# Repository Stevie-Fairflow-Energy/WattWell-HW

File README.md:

# Aim of the project
WattWell - An inverter, built for a lifetime. 
A home inverter, to interface battery systems and PV systems with the UK and EU electricity grids.

The WattWell must be:
- Durable
- Repairable
- Open-Source

The main goal of the project is to develop an open source inverter (Hardware and Software).  
The initial configuration of the project will be a single phase, 5 kW inverter. 

An important part of the project is to be able to work with different types of switching components (IGBT/MOSFET). Nowadays, we often see that inverters are replaced after 10 years but they keep working or some faulty inverters that are not easily repared because the design is not modular or easy to fix.

Then, the goal is to design an Open Source inverter that is modular to be easy to be fixed and flexible enough to have differents functionalities (batteries/PV/...)

The project will be divided into different "workpackages" based on the functional blocks needed to make the whole system work. These functional blocks are called "Modules", and may be split into further modules where necessary. The diagram below shows the module definitions we are currently working to. 

1. Supervisory control: development of the main control board able to get the measurements, generate references, ... This board embeds the main mcu.
2. Inverter Board
3. DC/DC converter: Able to take a variable DC input (48V +/- 20%) and output a stable DC output controllable between 360 V and 500 V.
4. DC Link: A DC link capable of self-protection
5. A DC filter for smooth input/output
6. DC Protections for over-current and over-voltage protection
7. DC connections for physically connecting the DC source to WattWell
8.  AC filter for smooth sine wave input/output
9. AC protection for over-current and over-voltage protection. Required for compatibility with grid codes.
10. Connections for phsyically conecting the external electrical system to WattWell
11. Human Machine Interface (HMI) to act as the interface between the user and the supervisory control

For the Inverter board, two sub-modules are assumed:
1. Control and Driver board: interface between the supervisory control board and power switch (IGBT's/Mosfet's). The driver board needs to generate the PWM signals based on a reference from the supervisor.
2. Power circuit: power circuit of the inverter

# Expected functionalities

- Being able (and allowed) to be connected to the European grid
- MPPT for solar panels (with DC/DC)
- Battery connection
- Communication capabilities (serial,...)
- Working in islanding mode (offgrid)

# 1. Supervisory control board:

For the supervisory control, the firmware on the main mcu should have (main mcu based on STM32G434):

1. Low level drivers
2. Basics functionalities (bootloader, debug uart, pll,...)
3. Advanced functionalities (power management, MPPT, state machine)

The main control board will be able to measure:
1.  3AC voltages (max 400V) - ADC min 14bits
2.  2DC voltages (max 1500V) -ADC min 14bits
3.  4AC/DC current measurement - ADC min 14bits
4.  Temperature measurement

The main control board will have the following interface:
1.  2X UART(1X to RS485; 1X to USB)
2.  1xSPI
3.  2xI2C
4.  1xCAN
5.  6X PWM's
6.  6X DO's
7.  6X DI's
8.  6X AI'S (temp from IGBT/Mos)

Other functions:
1.  Debug LED
2.  RTC (supercap based)
3.  Additionnal ROM (TBD)
4.  Watchdog
5.  Power supply for IGBT's/Mosfets

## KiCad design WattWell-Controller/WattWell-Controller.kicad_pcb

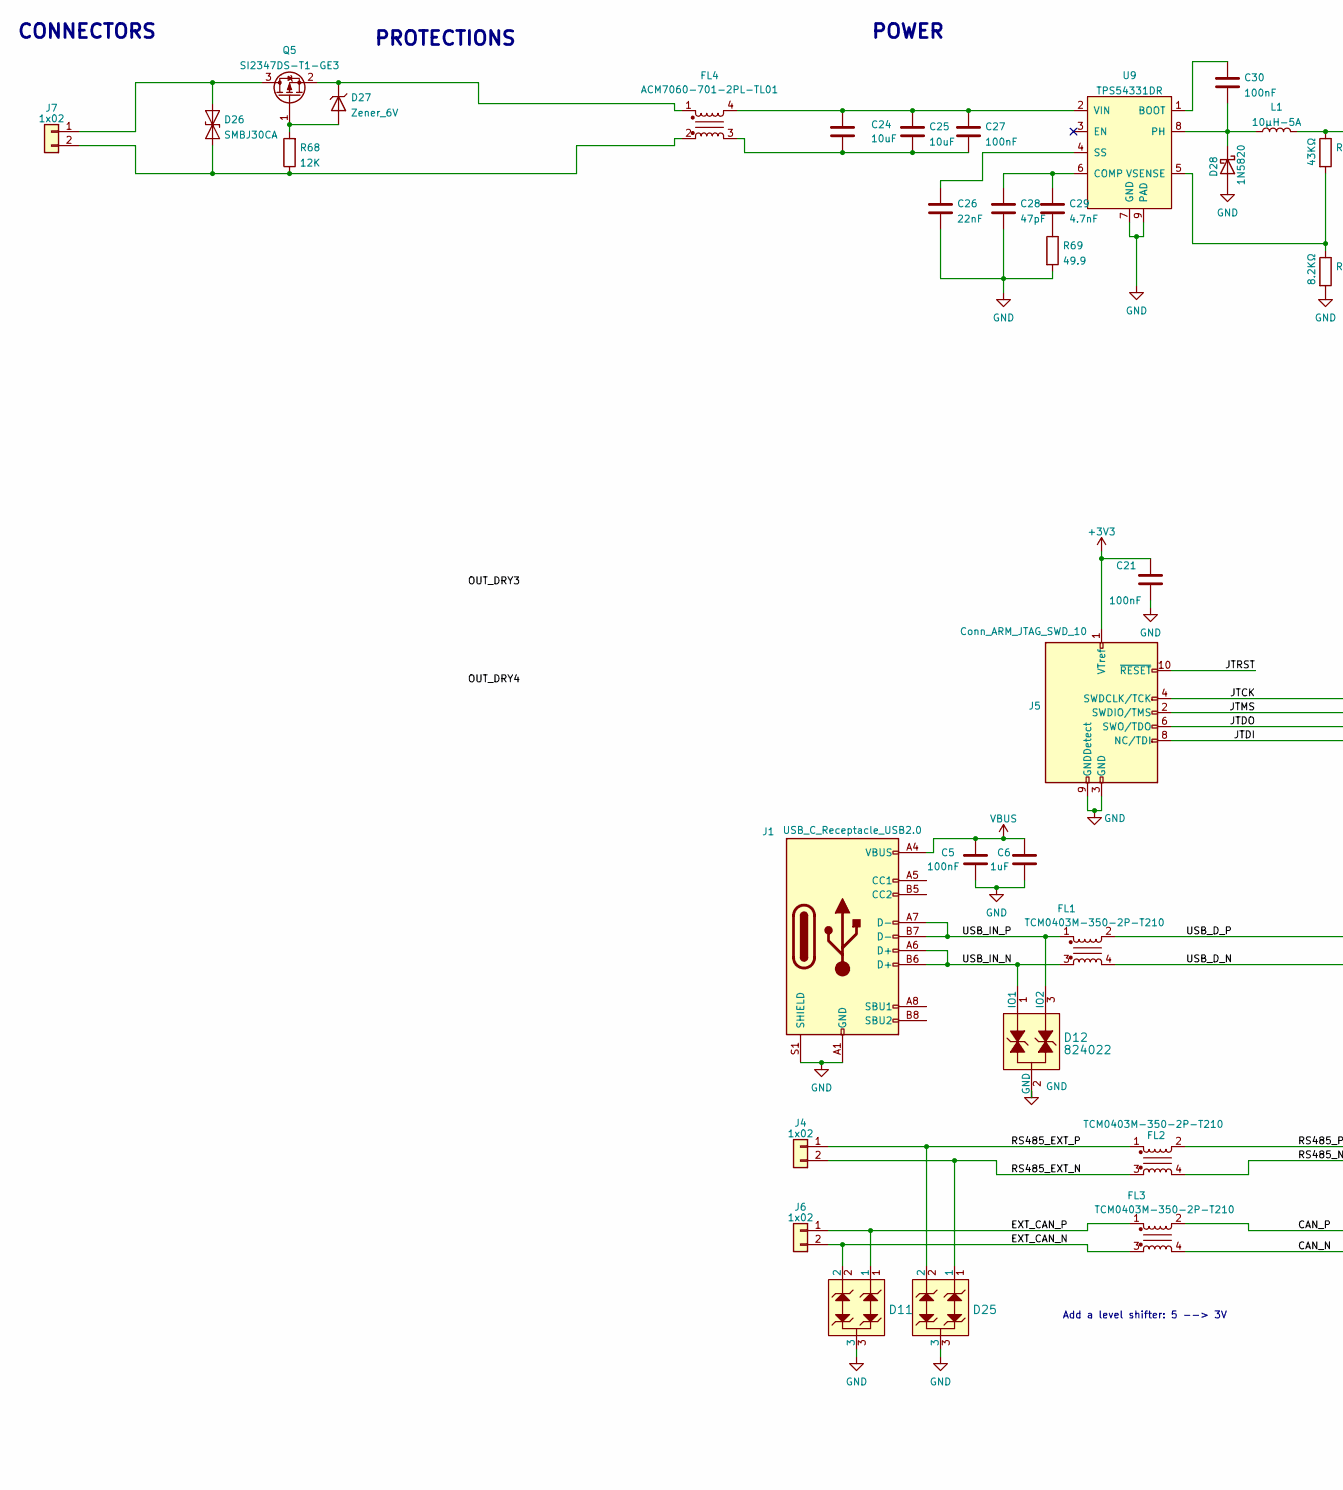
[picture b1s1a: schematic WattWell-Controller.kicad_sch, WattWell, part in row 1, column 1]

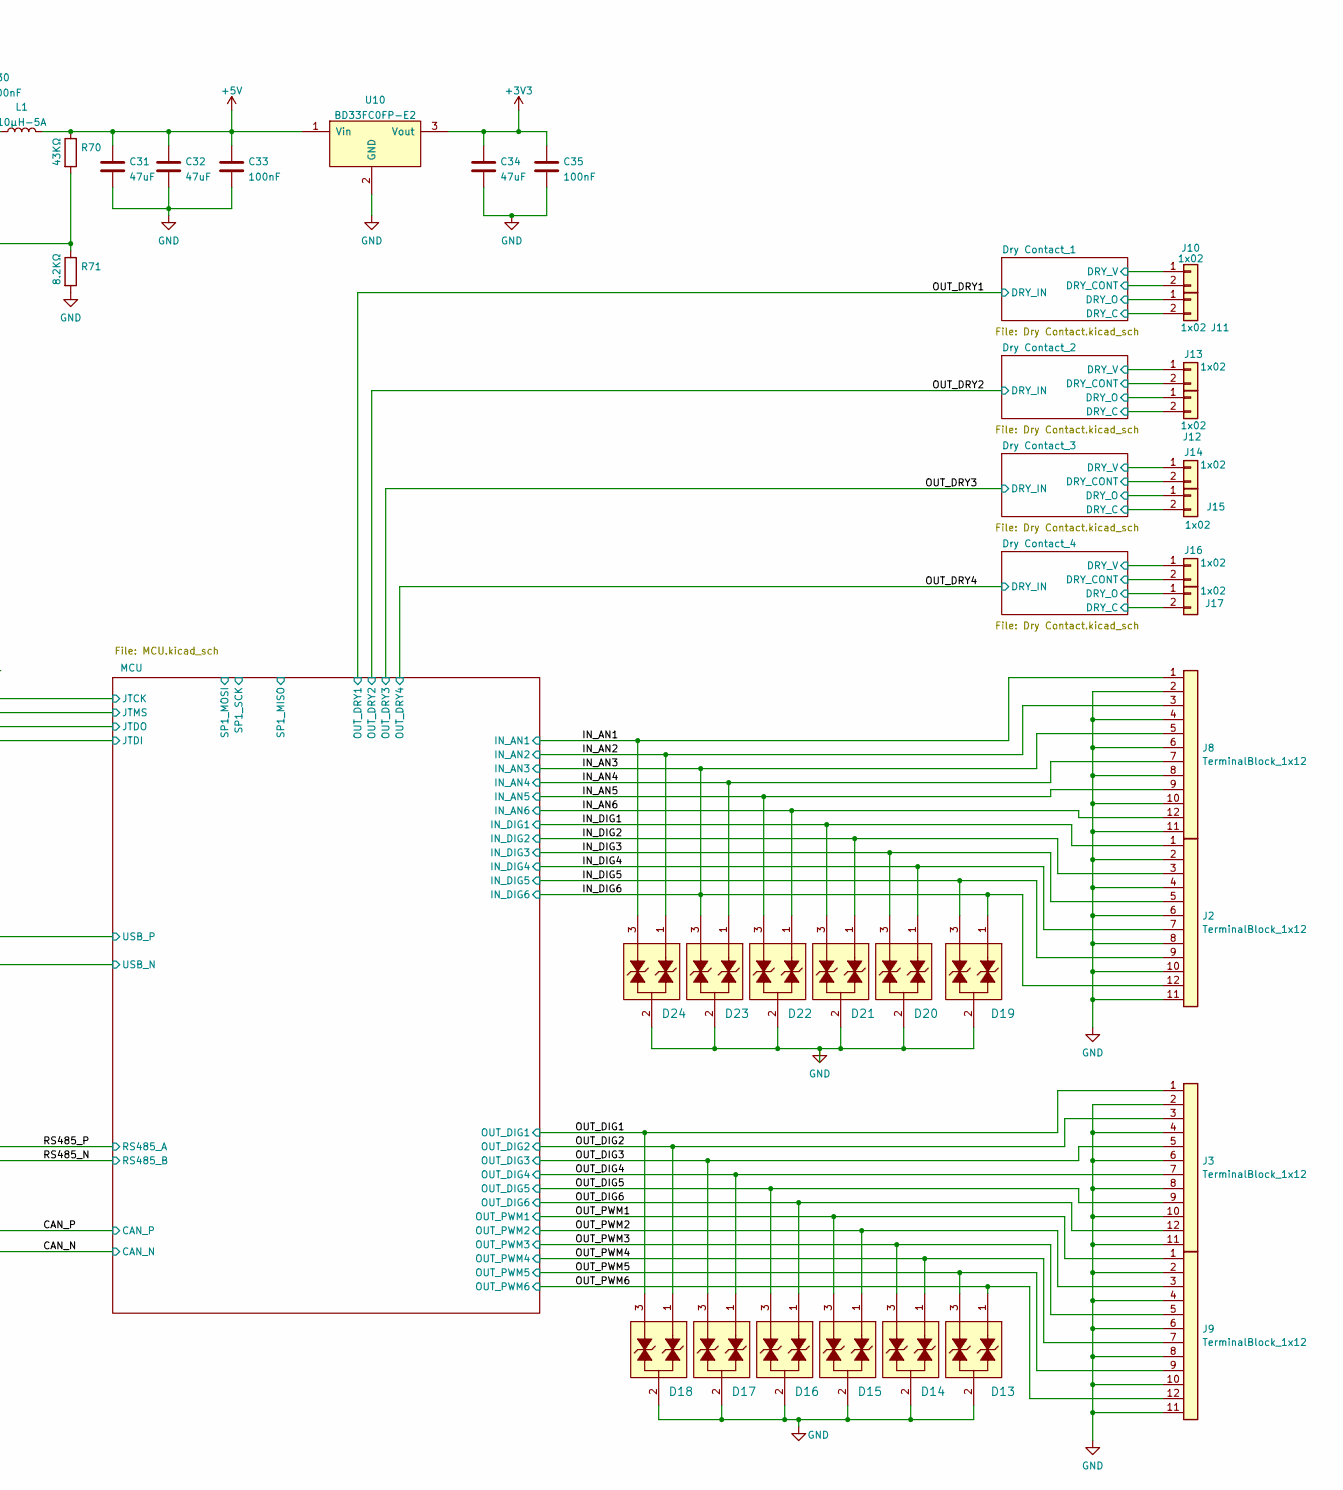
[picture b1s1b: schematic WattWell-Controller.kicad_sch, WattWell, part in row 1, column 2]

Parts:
C5, C21, C27, C30, C33, C35: 100nF; C_0603_1608Metric; Tolerance 10%; Voltage 50V; MPN CL10B104KB8NNNC
C6: 1uF; C_0603_1608Metric; Tolerance 10%; Voltage 25V; MPN CL10B105KA8NNNC
C24, C25: 10uF; C_1206_3216Metric; Tolerance 20%; Voltage 50V; MPN GRT31CR61H106ME01L
C26: 22nF; C_0603_1608Metric; Tolerance 10%; Voltage 50V; MPN CL10B223KB8WPNC
C28: 47pF; C_0603_1608Metric; Tolerance 10%; Voltage 50V; MPN 885012006055
C29: 4.7nF; C_0603_1608Metric; Tolerance 10%; Voltage 50V; MPN CL10B472KB8NNNC
C31, C32, C34: 47uF; C_1206_3216Metric; Tolerance 10%; Voltage 10V; MPN GRT31CR61A476KE13L
D11, D25: TVS_2-Channel-7V; SOT-23; MPN CDSOT23-SM712
D12: 824022; SOT-23; MPN 824022
D13, D14, D15, D16, D17, D18, D19, D20, D21, D22, D23, D24: PESD3V3L2BT; SOT-23; MPN PESD3V3L2BT,215
D26: SMBJ30CA; D_SMB; MPN SMBJ30CA
D27: Zener_6V; D_SOD-123; Voltage 6V; MPN MMSZ5233B-E3-08
D28: 1N5820; D_DO-201AD_P15.24mm_Horizontal
FL1, FL2, FL3: TCM0403M-350-2P-T210; Choke_TDK_TCM0403M-350-2P-T210; Manufacturer Part Number TCM0403M-350-2P-T210
FL4: ACM7060-701-2PL-TL01; ChokeSMD_ACM7060; MPN ACM7060-701-2PL-TL01
J1: USB_C_Receptacle_USB2.0; USB_C_Receptacle_GCT_USB4105-xx-A_16P_TopMnt_Horizontal; MPN USB4105-GF-A-120
J2, J3, J8, J9: TerminalBlock_1x12; TerminalBlock_Phoenix_MKDS-3-12-5.08_1x12_P5.08mm_Horizontal; MPN 1795763
J4, J6, J7, J10, J11, J12, J13, J14, J15, J16, J17: 1x02; WURTH-691312510002; MPN 691312510002
J5: Conn_ARM_JTAG_SWD_10; PinHeader_2x05_P2.54mm_Vertical_SMD; MPN FTSH-105-01-L-DV-K
L1: 10μH-5A; Inductor_Wurth_XHMI-6060; MPN 74439346100
Q5: SI2347DS-T1-GE3; SOT-23; MPN SI2347DS-T1-GE3
R68: 12K; R_0603_1608Metric; MPN RT0603FRE0712KL
R69: 49.9; R_0603_1608Metric; Tolerance 1%; MPN TNPW020149R9BEED
R70: 43KΩ; R_0603_1608Metric; Tolerance 1%; MPN RC0603FR-0743KL
R71: 8.2KΩ; R_0603_1608Metric; Tolerance 1%; MPN ERJ-3EKF8201V
U9: TPS54331DR; SOIC-8-1EP_3.9x4.9mm_P1.27mm_EP2.29x3mm_ThermalVias; MPN TPS54331DR
U10: BD33FC0FP-E2; TO-252-2; MPN BD33FC0FP-E2

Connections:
+3V3: C21.1, C34.1, C35.1, J5.1 (VTref), U10.3 (Vout); also elsewhere on the board
+5V: C31.1, C32.1, C33.1, L1.2, R70.1, U10.1 (Vin); also elsewhere on the board
/CAN_N: FL3.4; also elsewhere on the board
/CAN_P: FL3.2; also elsewhere on the board
/Dry Contact_1/DRY1_C: J11.2; also elsewhere on the board
/Dry Contact_1/DRY1_O: J11.1; also elsewhere on the board
/Dry Contact_1/DRY_CONT: J10.2; also elsewhere on the board
/Dry Contact_1/DRY_V: J10.1; also elsewhere on the board
/Dry Contact_2/DRY1_C: J12.2; also elsewhere on the board
/Dry Contact_2/DRY1_O: J12.1; also elsewhere on the board
/Dry Contact_2/DRY_CONT: J13.2; also elsewhere on the board
/Dry Contact_2/DRY_V: J13.1; also elsewhere on the board
/Dry Contact_3/DRY1_C: J15.2; also elsewhere on the board
/Dry Contact_3/DRY1_O: J15.1; also elsewhere on the board
/Dry Contact_3/DRY_CONT: J14.2; also elsewhere on the board
/Dry Contact_3/DRY_V: J14.1; also elsewhere on the board
/Dry Contact_4/DRY1_C: J17.2; also elsewhere on the board
/Dry Contact_4/DRY1_O: J17.1; also elsewhere on the board
/Dry Contact_4/DRY_CONT: J16.2; also elsewhere on the board
/Dry Contact_4/DRY_V: J16.1; also elsewhere on the board
/EXT_CAN_N: D11.2, FL3.3, J6.2
/EXT_CAN_P: D11.1, FL3.1, J6.1
/IN_AN1: D24.3, J8.1; also elsewhere on the board
/IN_AN2: D24.1, J8.3; also elsewhere on the board
/IN_AN3: D19.1, D23.3, J2.12 (Pin_8), J8.5; also elsewhere on the board
/IN_AN4: D23.1, J8.7 (Pin_10); also elsewhere on the board
/IN_AN5: D22.3, J8.9 (Pin_12); also elsewhere on the board
/IN_AN6: D22.1, J8.12 (Pin_8); also elsewhere on the board
/IN_DIG1: D21.3, J2.1; also elsewhere on the board
/IN_DIG2: D21.1, J2.3; also elsewhere on the board
/IN_DIG3: D20.3, J2.5; also elsewhere on the board
/IN_DIG4: D20.1, J2.7 (Pin_10); also elsewhere on the board
/IN_DIG5: D19.3, J2.9 (Pin_12); also elsewhere on the board
/JTCK: J5.4 (SWDCLK/TCK); also elsewhere on the board
/JTDI: J5.8 (NC/TDI); also elsewhere on the board
/JTDO: J5.6 (SWO/TDO); also elsewhere on the board
/JTMS: J5.2 (SWDIO/TMS); also elsewhere on the board
/JTRST: J5.10 (~RESET)
/OUT_DIG1: D18.3, J3.1; also elsewhere on the board
/OUT_DIG2: D18.1, J3.3; also elsewhere on the board
/OUT_DIG3: D17.3, J3.5; also elsewhere on the board
/OUT_DIG4: D17.1, J3.7 (Pin_10); also elsewhere on the board
/OUT_DIG5: D16.3, J3.9 (Pin_12); also elsewhere on the board
/OUT_DIG6: D16.1, J3.12 (Pin_8); also elsewhere on the board
/OUT_PWM1: D15.3, J9.1; also elsewhere on the board
/OUT_PWM2: D15.1, J9.3; also elsewhere on the board
/OUT_PWM3: D14.3, J9.5; also elsewhere on the board
/OUT_PWM4: D14.1, J9.7 (Pin_10); also elsewhere on the board
/OUT_PWM5: D13.3, J9.9 (Pin_12); also elsewhere on the board
/OUT_PWM6: D13.1, J9.12 (Pin_8); also elsewhere on the board
/RS485_EXT_N: D25.1, FL2.3, J4.2
/RS485_EXT_P: D25.2, FL2.1, J4.1
/RS485_N: FL2.4; also elsewhere on the board
/RS485_P: FL2.2; also elsewhere on the board
/USB_D_N: FL1.4; also elsewhere on the board
/USB_D_P: FL1.2; also elsewhere on the board
/USB_IN_N: D12.1 (IO1), FL1.3, J1.A6 (D+), J1.B6 (D+)
/USB_IN_P: D12.3 (IO2), FL1.1, J1.A7 (D-), J1.B7 (D-)
GND: C5.2, C6.2, C21.2, C26.2, C28.2, C31.2, C32.2, C33.2, C34.2, C35.2, D11.3, D12.2 (GND), D13.2, D14.2, D15.2, D16.2, D17.2, D18.2, D19.2, D20.2, D21.2, D22.2, D23.2, D24.2, D25.3, D28.2 (A), J1.A1 (GND), J1.A12 (GND), J1.B1 (GND), J1.B12 (GND), J1.S1 (SHIELD), J2.2, J2.4, J2.6, J2.8 (Pin_11), J2.10 (Pin_13), J2.11 (Pin_7), J3.2, J3.4, J3.6, J3.8 (Pin_11), J3.10 (Pin_13), J3.11 (Pin_7), J5.3 (GND), J5.5 (GND), J5.9 (GNDDetect), J8.2, J8.4, J8.6, J8.8 (Pin_11), J8.10 (Pin_13), J8.11 (Pin_7), J9.2, J9.4, J9.6, J9.8 (Pin_11), J9.10 (Pin_13), J9.11 (Pin_7), R69.2, R71.2, U9.7 (GND), U9.9 (PAD), U10.2 (GND); also elsewhere on the board
unnamed: C24.2, C25.2, C27.2, FL4.3
unnamed: C29.2, R69.1
unnamed: D26.1 (A1), FL4.2, J7.2, R68.1
unnamed: D26.2 (A2), J7.1, Q5.3 (D)
unnamed: D27.2 (A), Q5.1 (G), R68.2
unnamed: D27.1 (K), FL4.1, Q5.2 (S)
unnamed: C30.2, D28.1 (K), L1.1, U9.8 (PH)
unnamed: C30.1, U9.1 (BOOT)
unnamed: C28.1, C29.1, U9.6 (COMP)
unnamed: C26.1, U9.4 (SS)
unnamed: C24.1, C25.1, C27.1, FL4.4, U9.2 (VIN)
unnamed: R70.2, R71.1, U9.5 (VSENSE)
VBUS: C5.1, C6.1, J1.A4 (VBUS), J1.A9 (VBUS), J1.B4 (VBUS), J1.B9 (VBUS); also elsewhere on the board

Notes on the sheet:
CONNECTORS
POWER
Add a level shifter: 5 --> 3V
PROTECTIONS

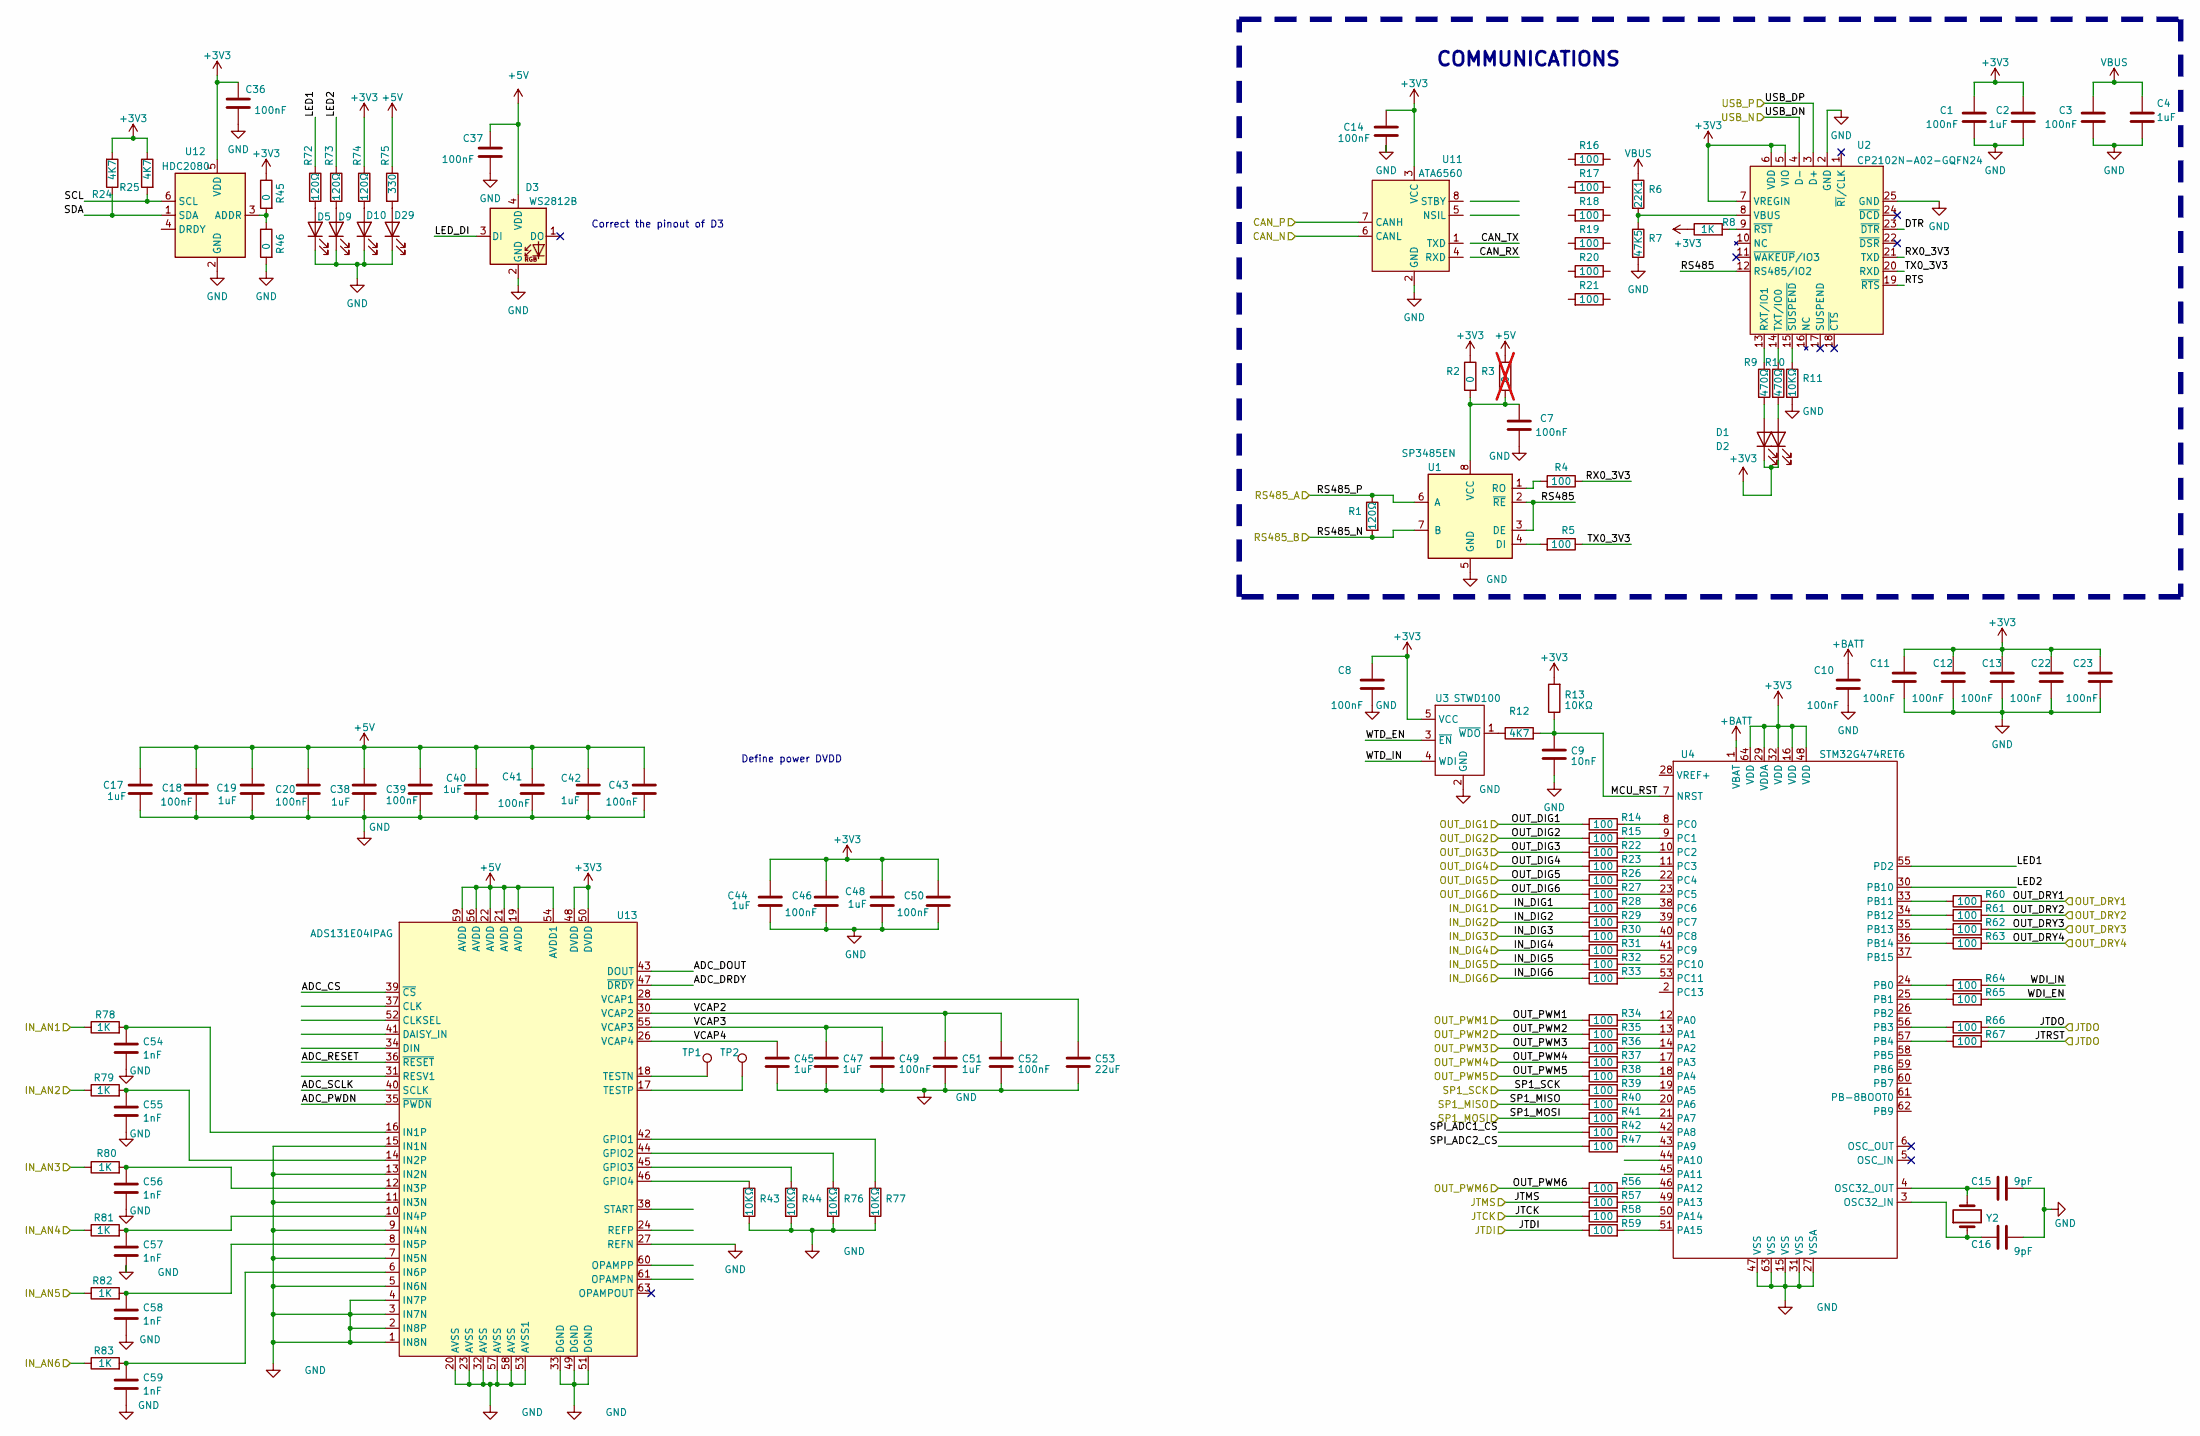
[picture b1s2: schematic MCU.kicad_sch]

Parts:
C1, C3, C7, C8, C10, C11, C12, C13, C14, C18, C20, C22, C23, C36, C37, C39, C41, C43, C46, C49, C50, C52: 100nF; C_0603_1608Metric; Tolerance 10%; Voltage 50V; MPN CL10B104KB8NNNC
C2, C4, C17, C19, C38, C40, C42, C44, C45, C47, C48, C51: 1uF; C_0603_1608Metric; Tolerance 10%; Voltage 25V; MPN CL10B105KA8NNNC
C9: 10nF; C_0603_1608Metric; Tolerance 10%; Voltage 50V; MPN CL10B103KB8NNNC
C15, C16: 9pF; C_0603_1608Metric; Tolerance 0.5%; Voltage 50VDC; MPN 0603N9R0D500CT
C53: 22uF; C_1206_3216Metric; Tolerance 20%; Voltage 10V; MPN CL31B226MPHNNNE
C54, C55, C56, C57, C58, C59: 1nF; C_0603_1608Metric; Tolerance 10%; Voltage 50V; MPN CL10B102KB8NNNC
D1, D2: LED_Small; LED_0603_1608Metric; MPN 150060RS55040
D3: WS2812B; LED_WS2812B_PLCC4_5.0x5.0mm_P3.2mm; Manufacturer Part Number 4684
D5, D9, D10, D29: 150060RS55040; LED_0603_1608Metric; MPN 150060RS55040
R1, R72, R73, R74: 120Ω; R_0603_1608Metric; Tolerance 5%; MPN CR0603-FX-1200ELF
R2, R45, R46: 0; R_0603_1608Metric; MPN RC0603JR-070RL
R3: 0; R_0603_1608Metric; MPN RC0603JR-070RL; not fitted
R4, R5, R14, R15, R16, R17, R18, R19, R20, R21, R22, R23, R26, R27, R28, R29, R30, R31, R32, R33, R34, R35, R36, R37, R38, R39, R40, R41, R42, R47, R56, R57, R58, R59, R60, R61, R62, R63, R64, R65, R66, R67: 100; R_0603_1608Metric; Tolerance 1%; MPN RC0603FR-07100RL
R6: 22K1; R_0603_1608Metric; MPN CR0603-FX-2212ELF
R7: 47K5; R_0603_1608Metric; MPN RT0603DRE0747K5L
R8, R78, R79, R80, R81, R82, R83: 1K; R_0603_1608Metric; Tolerance 1%; MPN RC0603FR-071KL
R9, R10: 470Ω; R_0603_1608Metric; Tolerance 5%; MPN CRCW0603470RJNEBC
R11, R13, R43, R44, R76, R77: 10KΩ; R_0603_1608Metric; Tolerance 1%; MPN ERJ-3EKF1002V
R12, R24, R25: 4K7; R_0603_1608Metric; Tolerance 1%; MPN CRGH0603F4K7
R75: 330; R_0603_1608Metric; Tolerance 1%; MPN AF0402JR-07330RL
TP1, TP2: TestPoint_1.5mm; TestPoint_Pad_D1.5mm
U1: SP3485EN; SOIC-8_3.9x4.9mm_P1.27mm; Manufacturer Part Number MAX3072EASA+
U2: CP2102N-A02-GQFN24; QFN-24-1EP_4x4mm_P0.5mm_EP2.6x2.6mm; MPN CP2102N-A02-GQFN24
U3: STWD100; SOT-23-5; Manufacturer Part Number STWD100YNWWY3F
U4: LQFP-64_10x10mm_P0.5mm; Manufacturer Part Number STM32G474RET6
U11: ATA6560; SOIC-8_3.9x4.9mm_P1.27mm; Manufacturer Part Number ATA6560-GAQW-N
U12: HDC2080; Texas_PWSON-N6; MPN HDC2080DMBT
U13: LQFP-64_10x10mm_P0.5mm; MPN ADS131E04IPAG
Y2: Crystal; Oscillator_SMD_ECS_2520MV-xxx-xx-4Pin_2.5x2.0mm; MPN ECS-.327-9-34QCS-TR9

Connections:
+3V3: C1.1, C2.1, C8.1, C11.1, C12.1, C13.1, C14.1, C22.1, C23.1, C36.1, C44.1, C46.1, C48.1, C50.1, D1.2 (K), D2.2 (K), R2.1, R8.1, R13.2, R24.2, R25.1, R45.1, R74.1, U2.5 (VIO), U2.6 (VDD), U2.7 (VREGIN), U3.5 (VCC), U4.16 (VDD), U4.29 (VDDA), U4.32 (VDD), U4.48 (VDD), U4.64 (VDD), U11.3 (VCC), U12.5 (VDD), U13.48 (DVDD), U13.50 (DVDD); also elsewhere on the board
+5V: C17.1, C18.1, C19.1, C20.1, C37.1, C38.1, C39.1, C40.1, C41.1, C42.1, C43.1, D3.4 (VDD), R3.1, R75.1, U13.19 (AVDD), U13.21 (AVDD), U13.22 (AVDD), U13.54 (AVDD1), U13.56 (AVDD), U13.59 (AVDD); also elsewhere on the board
+BATT: C10.1, U4.1 (VBAT)
/CAN_N: U11.6 (CANL); also elsewhere on the board
/CAN_P: U11.7 (CANH); also elsewhere on the board
/IN_AN1: R78.1; also elsewhere on the board
/IN_AN2: R79.1; also elsewhere on the board
/IN_AN3: R33.1, R80.1; also elsewhere on the board
/IN_AN4: R81.1; also elsewhere on the board
/IN_AN5: R82.1; also elsewhere on the board
/IN_AN6: R83.1; also elsewhere on the board
/IN_DIG1: R28.1; also elsewhere on the board
/IN_DIG2: R29.1; also elsewhere on the board
/IN_DIG3: R30.1; also elsewhere on the board
/IN_DIG4: R31.1; also elsewhere on the board
/IN_DIG5: R32.1; also elsewhere on the board
/JTCK: R58.1; also elsewhere on the board
/JTDI: R59.1; also elsewhere on the board
/JTDO: R66.2, R67.2; also elsewhere on the board
/JTMS: R57.1; also elsewhere on the board
/MCU/ADC_CS: U13.39 (~CS)
/MCU/ADC_DOUT: U13.43 (DOUT)
/MCU/ADC_DRDY: U13.47 (~DRDY)
/MCU/ADC_PWDN: U13.35 (~PWDN)
/MCU/ADC_RESET: U13.36 (~RESET)
/MCU/ADC_SCLK: U13.40 (SCLK)
/MCU/DTR: U2.23 (~DTR)
/MCU/LED1: R72.1, U4.55 (PD2)
/MCU/LED2: R73.1, U4.30 (PB10)
/MCU/LED_DI: D3.3 (DI)
/MCU/MCU_RST: C9.2, R12.2, R13.1, U4.7 (NRST)
/MCU/RS485: U1.2 (~RE), U1.3 (DE), U2.12 (RS485/IO2)
/MCU/RTS: U2.19 (~RTS)
/MCU/RX0_3V3: R4.1, U2.21 (TXD)
/MCU/SCL: R25.2, U12.6 (SCL)
/MCU/SDA: R24.1, U12.1 (SDA)
/MCU/SP1_MISO: R40.1
/MCU/SP1_MOSI: R41.1
/MCU/SP1_SCK: R39.1
/MCU/SPI_ADC1_CS: R42.1
/MCU/SPI_ADC2_CS: R47.1
/MCU/TX0_3V3: R5.1, U2.20 (RXD)
/MCU/VCAP2: C51.1, C52.1, U13.30 (VCAP2)
/MCU/VCAP3: C47.1, C49.1, U13.55 (VCAP3)
/MCU/VCAP4: C45.1, U13.26 (VCAP4)
/MCU/WDI_EN: R65.2
/MCU/WDI_IN: R64.2
/MCU/WTD_EN: U3.3 (~EN)
/MCU/WTD_IN: U3.4 (WDI)
/OUT_DIG1: R14.1; also elsewhere on the board
/OUT_DIG2: R15.1; also elsewhere on the board
/OUT_DIG3: R22.1; also elsewhere on the board
/OUT_DIG4: R23.1; also elsewhere on the board
/OUT_DIG5: R26.1; also elsewhere on the board
/OUT_DIG6: R27.1; also elsewhere on the board
/OUT_DRY1: R60.2; also elsewhere on the board
/OUT_DRY2: R61.2; also elsewhere on the board
/OUT_DRY3: R62.2; also elsewhere on the board
/OUT_DRY4: R63.2; also elsewhere on the board
/OUT_PWM1: R34.1; also elsewhere on the board
/OUT_PWM2: R35.1; also elsewhere on the board
/OUT_PWM3: R36.1; also elsewhere on the board
/OUT_PWM4: R37.1; also elsewhere on the board
/OUT_PWM5: R38.1; also elsewhere on the board
/OUT_PWM6: R56.1; also elsewhere on the board
/RS485_N: R1.2, U1.7 (B); also elsewhere on the board
/RS485_P: R1.1, U1.6 (A); also elsewhere on the board
/USB_D_N: U2.4 (D-); also elsewhere on the board
/USB_D_P: U2.3 (D+); also elsewhere on the board
GND: C1.2, C2.2, C3.2, C4.2, C7.2, C8.2, C9.1, C10.2, C11.2, C12.2, C13.2, C14.2, C15.2, C16.2, C17.2, C18.2, C19.2, C20.2, C22.2, C23.2, C36.2, C37.2, C38.2, C39.2, C40.2, C41.2, C42.2, C43.2, C44.2, C45.2, C46.2, C47.2, C48.2, C49.2, C50.2, C51.2, C52.2, C53.2, C54.2, C55.2, C56.2, C57.2, C58.2, C59.2, D3.2 (GND), D5.2 (K), D9.2 (K), D10.2 (K), D29.2 (K), R7.2, R11.2, R43.2, R44.2, R46.2, R76.2, R77.2, U1.5 (GND), U2.2 (GND), U2.25 (GND), U3.2 (GND), U4.15 (VSS), U4.27 (VSSA), U4.31 (VSS), U4.47 (VSS), U4.63 (VSS), U11.2 (GND), U12.2 (GND), U13.1 (IN8N), U13.2 (IN8P), U13.3 (IN7N), U13.4 (IN7P), U13.5 (IN6N), U13.7 (IN5N), U13.9 (IN4N), U13.11 (IN3N), U13.13 (IN2N), U13.15 (IN1N), U13.20 (AVSS), U13.23 (AVSS), U13.27 (REFN), U13.32 (AVSS), U13.33 (DGND), U13.49 (DGND), U13.51 (DGND), U13.53 (AVSS1), U13.57 (AVSS), U13.58 (AVSS); also elsewhere on the board
unnamed: D1.1 (A), R9.2
unnamed: D2.1 (A), R10.2
unnamed: D5.1 (A), R72.2
unnamed: D9.1 (A), R73.2
unnamed: D10.1 (A), R74.2
unnamed: D29.1 (A), R75.2
unnamed: R5.2, U1.4 (DI)
unnamed: R4.2, U1.1 (RO)
unnamed: C7.1, R2.2, R3.2, U1.8 (VCC)
unnamed: R9.1, U2.13 (RXT/IO1)
unnamed: R10.1, U2.14 (TXT/IO0)
unnamed: R6.2, R7.1, U2.8 (VBUS)
unnamed: R8.2, U2.9 (~RST)
unnamed: R11.1, U2.15 (~SUSPEND)
unnamed: R12.1, U3.1 (~WDO)
unnamed: C16.1, U4.3 (OSC32_IN), Y2.1
unnamed: C15.1, U4.4 (OSC32_OUT), Y2.2
unnamed: R34.2, U4.12 (PA0)
unnamed: R35.2, U4.13 (PA1)
unnamed: R36.2, U4.14 (PA2)
unnamed: R37.2, U4.17 (PA3)
unnamed: R38.2, U4.18 (PA4)
unnamed: R39.2, U4.19 (PA5)
unnamed: R40.2, U4.20 (PA6)
unnamed: R41.2, U4.21 (PA7)
unnamed: R42.2, U4.42 (PA8)
unnamed: R47.2, U4.43 (PA9)
unnamed: R56.2, U4.46 (PA12)
unnamed: R57.2, U4.49 (PA13)
unnamed: R58.2, U4.50 (PA14)
unnamed: R59.2, U4.51 (PA15)
unnamed: R64.1, U4.24 (PB0)
unnamed: R65.1, U4.25 (PB1)
unnamed: R66.1, U4.56 (PB3)
unnamed: R67.1, U4.57 (PB4)
unnamed: R60.1, U4.33 (PB11)
unnamed: R61.1, U4.34 (PB12)
unnamed: R62.1, U4.35 (PB13)
unnamed: R63.1, U4.36 (PB14)
unnamed: R14.2, U4.8 (PC0)
unnamed: R15.2, U4.9 (PC1)
unnamed: R22.2, U4.10 (PC2)
unnamed: R23.2, U4.11 (PC3)
unnamed: R26.2, U4.22 (PC4)
unnamed: R27.2, U4.23 (PC5)
unnamed: R28.2, U4.38 (PC6)
unnamed: R29.2, U4.39 (PC7)
unnamed: R30.2, U4.40 (PC8)
unnamed: R31.2, U4.41 (PC9)
unnamed: R32.2, U4.52 (PC10)
unnamed: R33.2, U4.53 (PC11)
unnamed: R45.2, R46.1, U12.3 (ADDR)
unnamed: R77.1, U13.42 (GPIO1)
unnamed: R76.1, U13.44 (GPIO2)
unnamed: R44.1, U13.45 (GPIO3)
unnamed: R43.1, U13.46 (GPIO4)
unnamed: C54.1, R78.2, U13.16 (IN1P)
unnamed: C55.1, R79.2, U13.14 (IN2P)
unnamed: C56.1, R80.2, U13.12 (IN3P)
unnamed: C57.1, R81.2, U13.10 (IN4P)
unnamed: C58.1, R82.2, U13.8 (IN5P)
unnamed: C59.1, R83.2, U13.6 (IN6P)
unnamed: TP1.1, U13.18 (TESTN)
unnamed: TP2.1, U13.17 (TESTP)
unnamed: C53.1, U13.28 (VCAP1)
VBUS: C3.1, C4.1, R6.1; also elsewhere on the board

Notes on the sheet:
COMMUNICATIONS
Define power DVDD
Correct the pinout of D3

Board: 2 copper layers, 225 parts (0 on the bottom side), 169 nets, no tracks yet.

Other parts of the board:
C18#2, C39#2, C46#2, C50#2: 100nF; C_0603_1608Metric
C20#2, C41#2, C43#2: 22uF; C_1206_3216Metric
D4, D6, D7, D8: 1N47xxA; D_DO-41_SOD81_P10.16mm_Horizontal
K1, K2, K3, K4: RZH3-1C4-D012; Relay_TE_RZH3-1C04-D012
Q1, Q2, Q3, Q4: MMSS8050-H-TP; SOT-23
R48, R49, R50, R51, R52, R53, R54, R55: 120Ω; R_0603_1608Metric
U5, U6, U7, U8: LTV-356T; SO-4_4.4x3.6mm_P2.54mm

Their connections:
+3V3: C46#2.1, C50#2.1; also elsewhere on the board
+5V: C18#2.1, C20#2.1, C39#2.1, C41#2.1, C43#2.1; also elsewhere on the board
/Dry Contact_1/DRY1_C: K1.12; also elsewhere on the board
/Dry Contact_1/DRY1_O: K1.14; also elsewhere on the board
/Dry Contact_1/DRY_CONT: K1.11; also elsewhere on the board
/Dry Contact_1/DRY_V: D4.1 (K), K1.A2, U5.4; also elsewhere on the board
/Dry Contact_2/DRY1_C: K2.12; also elsewhere on the board
/Dry Contact_2/DRY1_O: K2.14; also elsewhere on the board
/Dry Contact_2/DRY_CONT: K2.11; also elsewhere on the board
/Dry Contact_2/DRY_V: D6.1 (K), K2.A2, U6.4; also elsewhere on the board
/Dry Contact_3/DRY1_C: K3.12; also elsewhere on the board
/Dry Contact_3/DRY1_O: K3.14; also elsewhere on the board
/Dry Contact_3/DRY_CONT: K3.11; also elsewhere on the board
/Dry Contact_3/DRY_V: D7.1 (K), K3.A2, U7.4; also elsewhere on the board
/Dry Contact_4/DRY1_C: K4.12; also elsewhere on the board
/Dry Contact_4/DRY1_O: K4.14; also elsewhere on the board
/Dry Contact_4/DRY_CONT: K4.11; also elsewhere on the board
/Dry Contact_4/DRY_V: D8.1 (K), K4.A2, U8.4; also elsewhere on the board
/OUT_DRY1: R49.2; also elsewhere on the board
/OUT_DRY2: R51.2; also elsewhere on the board
/OUT_DRY3: R53.2; also elsewhere on the board
/OUT_DRY4: R55.2; also elsewhere on the board
GND: C18#2.2, C20#2.2, C39#2.2, C41#2.2, C43#2.2, C46#2.2, C50#2.2, U5.2, U6.2, U7.2, U8.2; also elsewhere on the board
GND1: Q1.2 (E), Q2.2 (E), Q3.2 (E), Q4.2 (E)
unnamed: D4.2 (A), K1.A1, Q1.3 (C)
unnamed: D6.2 (A), K2.A1, Q2.3 (C)
unnamed: D7.2 (A), K3.A1, Q3.3 (C)
unnamed: D8.2 (A), K4.A1, Q4.3 (C)
unnamed: Q1.1 (B), R48.1
unnamed: Q2.1 (B), R50.1
unnamed: Q3.1 (B), R52.1
unnamed: Q4.1 (B), R54.1
unnamed: R48.2, U5.3
unnamed: R49.1, U5.1
unnamed: R50.2, U6.3
unnamed: R51.1, U6.1
unnamed: R52.2, U7.3
unnamed: R53.1, U7.1
unnamed: R54.2, U8.3
unnamed: R55.1, U8.1

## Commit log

2025-01-14 Component placement continued
2025-05-28 Layout continued. Placement
2025-09-11 Placement continued Changed the order of Terminal block connectors
2025-09-12 Placement continued
2025-09-13 Placement continued ADC powered to 5V and 3.3
2025-09-13 Schematic and placement continued
2025-09-17 Added Blank SIMBA simulation file
    Getting things ready to make a simulation of the WattWell.
2025-09-17 First basic simulation of inverter power circuit and simple control
2025-09-17 Added energy monitoring for efficiency measurement
2025-09-22 Added screenshots of simulation progress
2025-09-22 Tried waveform generator for DC-DC converter
2025-09-22 Differential voltage probes for correct energy metering.
2025-09-22 Added simulation screenshots
2025-09-29 Added datasheets of potential components
2025-09-30 Added interfaces design
    Interfaces design has inverter that works as expected.
2025-09-30 Added instantaneous current protection
    Instantaneous current protection implemented within the H bridge module.
2025-09-30 Added a sample time to stop inconsistent graphing
2025-09-30 Simple thermal model setup for MOSFETs
2025-10-09 Update README.md
    Updated readme with a interface diagram and definition of more modules.
2025-10-09 Create Licence - CERN OHLV2-Permissive
2025-10-09 Create CERN-OHL-P licence
2025-10-14 SIMBA Simulation improvements - inverter control
    Simple current control with feed-forward voltage working in simulation.
2025-10-14 Minor simulation tweaks
    Minor tweaks to try current limiting.
    Added datasheet of relevant current transformer for fast protection.
2025-10-15 Tidied interfaces in simulation
2025-10-16 PID control added for current mode
    PID control added for current mode.
    Attempts to get AC sweep working, but unsuccessful.
2025-10-17 Working simple voltage PID control
    Working simple PID control, note that the response is not super smooth!
2025-10-17 Added limiter - more stable voltage control
